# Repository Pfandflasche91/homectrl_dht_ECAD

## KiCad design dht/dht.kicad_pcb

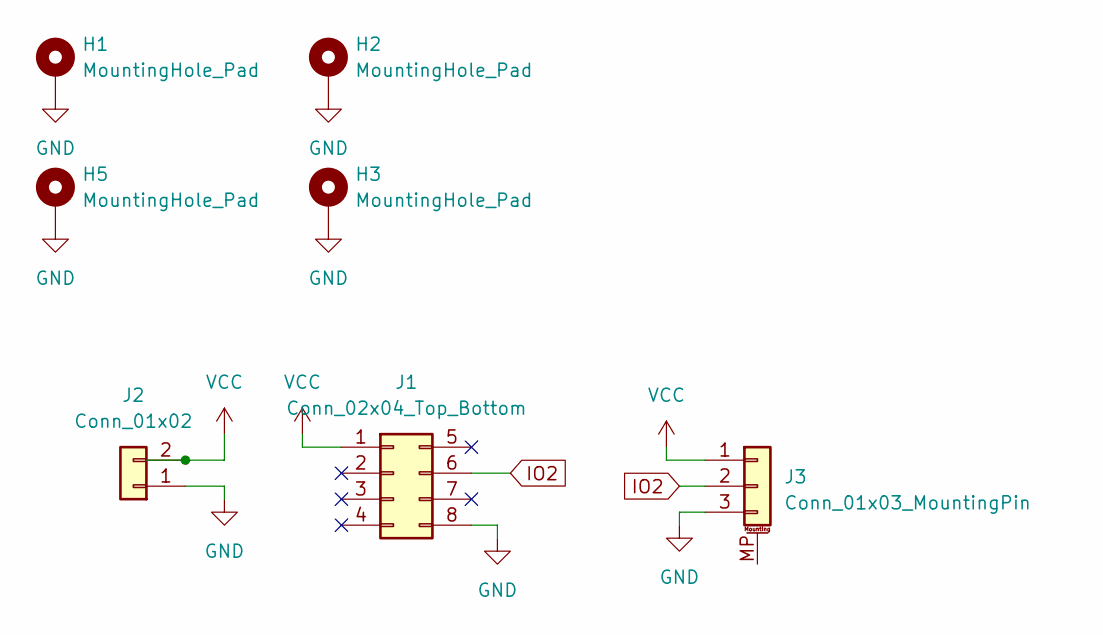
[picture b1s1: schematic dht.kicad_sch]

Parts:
H1, H2, H3, H5: MountingHole_Pad; MountingHole_3.2mm_M3_Pad_Via
J1: Conn_02x04_Top_Bottom; PinSocket_2x04_P2.54mm_Vertical
J2: Conn_01x02; Hirose_DF13-02P-1.25DSA_1x02_P1.25mm_Vertical
J3: Conn_01x03_MountingPin; PinHeader_1x03_P2.54mm_Vertical

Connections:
GND: H1.1, H2.1, H3.1, H5.1, J1.8, J2.1, J3.3
IO2: J1.6, J3.2
VCC: J1.1, J2.2, J3.1

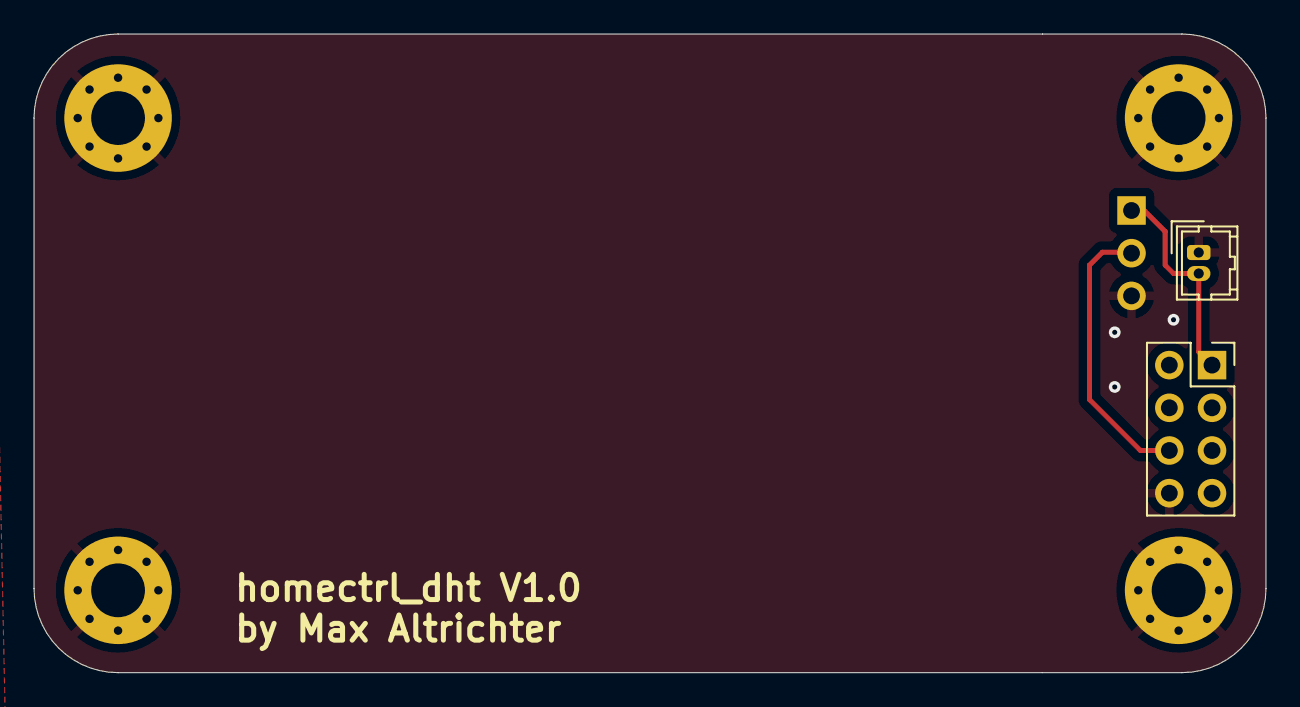
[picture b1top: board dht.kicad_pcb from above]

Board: 2 copper layers, 73.3 x 38.0 mm, 7 parts (1 on the bottom side), 3 nets.

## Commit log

2024-05-31 schematic done , parts aligned . rooting needed!
2024-06-01 orderd PCB V1 added step file for CAD
